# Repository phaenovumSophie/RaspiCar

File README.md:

# RaspiCar
A model car equipped with a Raspberry Pi, intended for experimenting with tools and algorithms for autonomous navigation

This is a simple platform for experimenting. At this stage clearly work in progress ...

The car is based on two stepper motors for the left and right driving wheel. In addition there is a free spinning wheel in the front. Driving direction is controlled by different speed settings for the motors. The car is capable of turning on the spot. Power is provided a by a LiPo battery of 3 cells.

Raspberry Pi:
=============
The Raspberry Pi provides navigation and overall management of the car. The navigations is based on the various sensors. The software is written primarily in Python. Prototype software is avaiable to support ultrasonic sensors, LiDAR, camera and a NRF24 module for remote control. There are also experiments with machine learning alogrithms (SciKit Learn). More to be developed and to follow.

Python files:
- io_ctrl.py - This module defines the I/Os for the Raspberry Pi and a tool to send commands to the motor driver via a serial interface
- much more to come ...

Motor Driver:
=============
In addition to the Raspberry Pi, there is a board comprising a 5V step down converter, a rp2040 microcontroller, a LCD and adapters for various devices such as LiDAR, distance sensors and more. The rp2040 generates the step and direction signals for the stepper motors, with this releasing the real time workload from the Raspberry Pi. The rp2040 interfaces with the Raspberry Pi via a serial interface running at115200 baud. The rp2040 also takes care of power management by raising a shutdown signal in case the battery voltage is running low. The software for the rp2040 is based on Arduino/C++

Arduino files for the motor driver:
- rp2040_motor_driver.ino: main program
- motors.cpp, motors.h: class to run the stepper motors
- display.cpp, display.h: class to run the display
- battery.cpp, battery.h: class to provide battery and power management

List of motor commands:
The Raspberry Pi sends commands via the serial interface and receives responses. This can easily by tested via a standard terminal tool (e.g. PUTTY).
- ME0,0 / ME1,1  - disables or enables motor A and B
- MP0,0 / MP1,1  - switches motor A and B on or off
- MD0,0 / MD1,1  - sets the direction of the motor (1 -> forward, 0 -> backward)
- MR<l>,<r> - sets the speed of the motors in rounds per minute. The range is 0 to 1500. Example: "MR200,500"
- DC - clears the display (title and message)
- DT - prints a title of up to 0 characters on line 1 of the display (maximum 20 characters)
- DM - prints a message of up to 40 character on line 2 and 3 of the display
- BV - returns the current battery voltage
- BS - returns the battery voltage and the system status, separated by comma 

List of system status:
  - 0 - STATUS_OK                   'OK' - all fine
  - 1 - STATUS_BAT_LOW              'BL' - Battery low, voltage below 10.5V
  - 2 - STATUS_BAT_SHUTDOWN         'BS' - Battery very low, shutdown requested due to low power, waiting for Raspi to respond
  - 3 - STATUS_BAT_EXTERNAL         'BE  - System running on 5V external power
  - 4 - STATUS_SHUTDOWN_REQUESTED   'SR' - Shutdwon requested by user, waiting for Raspi to respond
  - 5 - STATUS_SHUTDOWN_ACTIVE      'SX' - Shutdown in progress, power will be shut in less than 10 secs

SLW October 2022

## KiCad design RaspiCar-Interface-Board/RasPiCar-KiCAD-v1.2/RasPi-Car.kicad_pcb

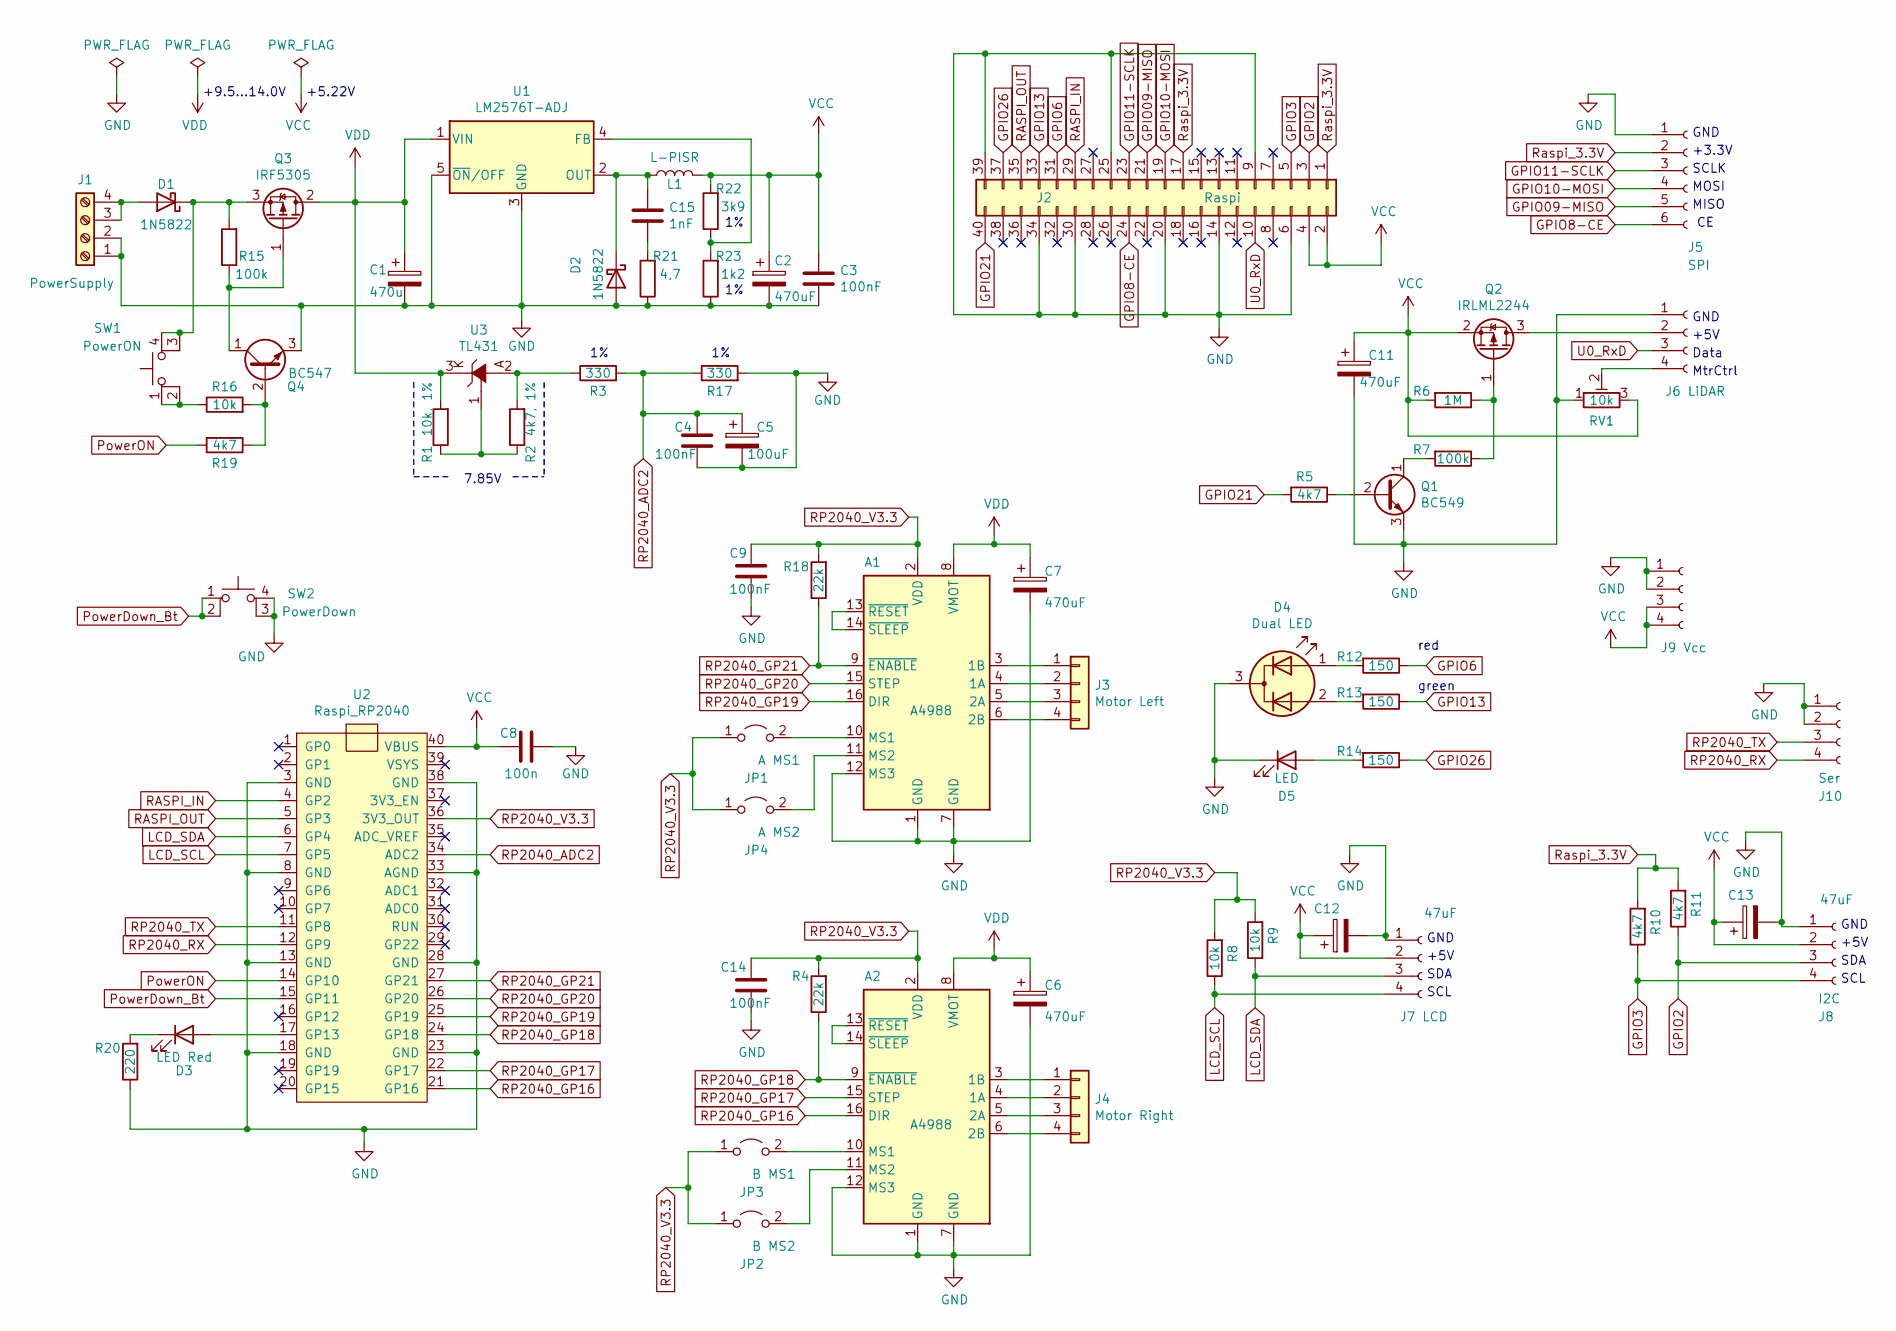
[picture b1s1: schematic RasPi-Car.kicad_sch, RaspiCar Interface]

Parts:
A1, A2: A4988; Pololu_Breakout-16_15.2x20.3mm
C1: 470u; CP_Radial_D8.0mm_P3.50mm
C2, C6, C7, C11: 470uF; CP_Radial_D8.0mm_P3.50mm
C3, C4, C9, C14: 100nF; C_Disc_D3.4mm_W2.1mm_P2.50mm
C5: 100uF; CP_Radial_D6.3mm_P2.50mm
C8: 100n; C_Disc_D3.4mm_W2.1mm_P2.50mm
C12, C13: 47uF; CP_Radial_D6.3mm_P2.50mm
C15: 1nF; C_Disc_D3.4mm_W2.1mm_P2.50mm
D1, D2: 1N5822; D_DO-201AE_P3.81mm_Vertical_KathodeUp
D3: LED Red; LED_D3.0mm
D4: Dual LED; LED_D3.0mm-3-center-kathode
D5: LED; LED_D3.0mm
J1: PowerSupply; ScrewTerminal_1x4
J2: Raspi; PinHeader_2x20_P2.54mm_Vertical
J3: Motor Left; PinHeader_1x04_P2.54mm_Vertical
J4: Motor Right; PinHeader_1x04_P2.54mm_Vertical
J5: SPI; PinHeader_1x06_P2.54mm_Vertical
J6: LiDAR; PinHeader_1x04_P2.54mm_Vertical
J7: LCD; PinHeader_1x04_P2.54mm_Vertical
J8: I2C; PinHeader_1x04_P2.54mm_Vertical
J9: Vcc; PinHeader_1x04_P2.54mm_Vertical
J10: Ser; PinHeader_1x04_P2.54mm_Vertical
JP1: A MS1; PinHeader_1x02_P2.54mm_Vertical
JP2: B MS2; PinHeader_1x02_P2.54mm_Vertical
JP3: B MS1; PinHeader_1x02_P2.54mm_Vertical
JP4: A MS2; PinHeader_1x02_P2.54mm_Vertical
L1: L-PISR; L-PISR-100
Q1: BC549; TO-92_HandSolder
Q2: IRLML2244; SOT-23
Q3: IRF5305; TO-220-3_Vertical
Q4: BC547; TO-92_HandSolder
R1: 10k, 1%; R_Axial_DIN0207_L6.3mm_D2.5mm_P7.62mm_Horizontal
R2: 4k7, 1%; R_Axial_DIN0207_L6.3mm_D2.5mm_P7.62mm_Horizontal
R3, R17: 330; R_Axial_DIN0207_L6.3mm_D2.5mm_P7.62mm_Horizontal
R4, R18: 22k; R_Axial_DIN0207_L6.3mm_D2.5mm_P7.62mm_Horizontal
R5, R10, R11, R19: 4k7; R_Axial_DIN0207_L6.3mm_D2.5mm_P7.62mm_Horizontal
R6: 1M; R_Axial_DIN0207_L6.3mm_D2.5mm_P7.62mm_Horizontal
R7, R15: 100k; R_Axial_DIN0207_L6.3mm_D2.5mm_P7.62mm_Horizontal
R8, R9, R16: 10k; R_Axial_DIN0207_L6.3mm_D2.5mm_P7.62mm_Horizontal
R12, R13: 150; R_Axial_DIN0207_L6.3mm_D2.5mm_P2.54mm_Vertical
R14: 150; R_Axial_DIN0207_L6.3mm_D2.5mm_P7.62mm_Horizontal
R20: 220; R_Axial_DIN0207_L6.3mm_D2.5mm_P7.62mm_Horizontal
R21: 4,7; R_Axial_DIN0207_L6.3mm_D2.5mm_P2.54mm_Vertical
R22: 3k9; R_Axial_DIN0207_L6.3mm_D2.5mm_P2.54mm_Vertical
R23: 1k2; R_Axial_DIN0207_L6.3mm_D2.5mm_P2.54mm_Vertical
RV1: 10k; R-Trim_horizontal
SW1: PowerON; SW_PUSH_6mm_H5mm
SW2: PowerDown; SW_PUSH_6mm_H5mm
U1: LM2576T-ADJ; TO-220-5_Vertical_tiny_heatsink
U2: Raspi_RP2040
U3: TL431; TO-92_HandSolder

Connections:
GND: A1.1 (GND), A1.7 (GND), A1.12 (MS3), A2.1 (GND), A2.7 (GND), A2.12 (MS3), C1.2, C2.2, C3.2, C4.1, C5.2, C6.2, C7.2, C8.1, C9.2, C11.2, C12.2, C13.2, C14.2, D2.2 (A), D4.3 (K), D5.1 (K), J1.1, J1.2, J2.6, J2.9, J2.14, J2.20, J2.25, J2.30, J2.34, J2.39, J5.1, J6.1, J7.1, J8.1, J9.1, J9.2, J10.1, J10.2, Q1.3 (E), Q4.3 (E), R17.2, R20.1, R21.1, R23.1, RV1.1, SW2.3 (K), SW2.4 (A), U1.3 (GND), U1.5 (~ON/OFF), U2.3 (GND), U2.8 (GND), U2.13 (GND), U2.18 (GND), U2.23 (GND), U2.28 (GND), U2.33 (AGND), U2.38 (GND)
GPIO2: J2.3, J8.3, R11.1
GPIO3: J2.5, J8.4, R10.1
GPIO6: J2.31, R12.1
GPIO8-CE: J2.24, J5.6
GPIO09-MISO: J2.21, J5.5
GPIO10-MOSI: J2.19, J5.4
GPIO11-SCLK: J2.23, J5.3
GPIO13: J2.33, R13.1
GPIO21: J2.40, R5.2
GPIO26: J2.37, R14.1
LCD_SCL: J7.4, R8.1, U2.7 (GP5)
LCD_SDA: J7.3, R9.1, U2.6 (GP4)
unnamed: A1.4 (1A), J3.2
unnamed: A1.3 (1B), J3.1
unnamed: A1.5 (2A), J3.3
unnamed: A1.6 (2B), J3.4
unnamed: A1.10 (MS1), JP1.2 (B)
unnamed: A1.11 (MS2), JP4.2 (B)
unnamed: A1.13 (~RESET), A1.14 (~SLEEP)
unnamed: A2.4 (1A), J4.2
unnamed: A2.3 (1B), J4.1
unnamed: A2.5 (2A), J4.3
unnamed: A2.6 (2B), J4.4
unnamed: A2.10 (MS1), JP3.2 (B)
unnamed: A2.11 (MS2), JP2.2 (B)
unnamed: A2.13 (~RESET), A2.14 (~SLEEP)
unnamed: C15.2, R21.2
unnamed: D1.2 (A), J1.3, J1.4
unnamed: D1.1 (K), Q3.3 (S), R15.2, SW1.3 (K), SW1.4 (A)
unnamed: C15.1, D2.1 (K), L1.1, U1.2 (OUT)
unnamed: D3.2 (A), U2.17 (GP13)
unnamed: D3.1 (K), R20.2
unnamed: D4.1 (A1), R12.2
unnamed: D4.2 (A2), R13.2
unnamed: D5.2 (A), R14.2
unnamed: J6.2, Q2.3 (D)
unnamed: J6.4, RV1.2
unnamed: Q1.2 (B), R5.1
unnamed: Q1.1 (C), R7.2
unnamed: Q2.1 (G), R6.1, R7.1
unnamed: Q3.1 (G), Q4.1 (C), R15.1
unnamed: Q4.2 (B), R16.2, R19.1
unnamed: R16.1, SW1.1, SW1.2
unnamed: R22.1, R23.2, U1.4 (FB)
unnamed: R2.2, R3.1, U3.2 (A)
unnamed: R1.1, R2.1, U3.1 (R)
PowerDown_Bt: SW2.1, SW2.2, U2.15 (GP11)
PowerON: R19.2, U2.14 (GP10)
RASPI_IN: J2.29, U2.4 (GP2)
RASPI_OUT: J2.35, U2.5 (GP3)
RP2040_ADC2: C4.2, C5.1, R3.2, R17.1, U2.34 (ADC2)
RP2040_GP16: A2.16 (DIR), U2.21 (GP16)
RP2040_GP17: A2.15 (STEP), U2.22 (GP17)
RP2040_GP18: A2.9 (~ENABLE), R4.1, U2.24 (GP18)
RP2040_GP19: A1.16 (DIR), U2.25 (GP19)
RP2040_GP20: A1.15 (STEP), U2.26 (GP20)
RP2040_GP21: A1.9 (~ENABLE), R18.1, U2.27 (GP21)
RP2040_RX: J10.4, U2.12 (GP9)
RP2040_TX: J10.3, U2.11 (GP8)
RP2040_V3.3: A1.2 (VDD), A2.2 (VDD), C9.1, C14.1, JP1.1 (A), JP2.1 (A), JP3.1 (A), JP4.1 (A), R4.2, R8.2, R9.2, R18.2, U2.36 (3V3_OUT)
Raspi_3.3V: J2.1, J2.17, J5.2, R10.2, R11.2
U0_RxD: J2.10, J6.3
VCC: C2.1, C3.1, C8.2, C11.1, C12.1, C13.1, J2.2, J2.4, J7.2, J8.2, J9.3, J9.4, L1.2, Q2.2 (S), R6.2, R22.2, RV1.3, U2.40 (VBUS)
VDD: A1.8 (VMOT), A2.8 (VMOT), C1.1, C6.1, C7.1, Q3.2 (D), R1.2, U1.1 (VIN), U3.3 (K)

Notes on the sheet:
SCL
+9.5...14.0V
+5V
7.85V
SDA
MtrCtrl
Data
SCLK
red
MISO
GND
+5.22V
+3.3V
MOSI
green

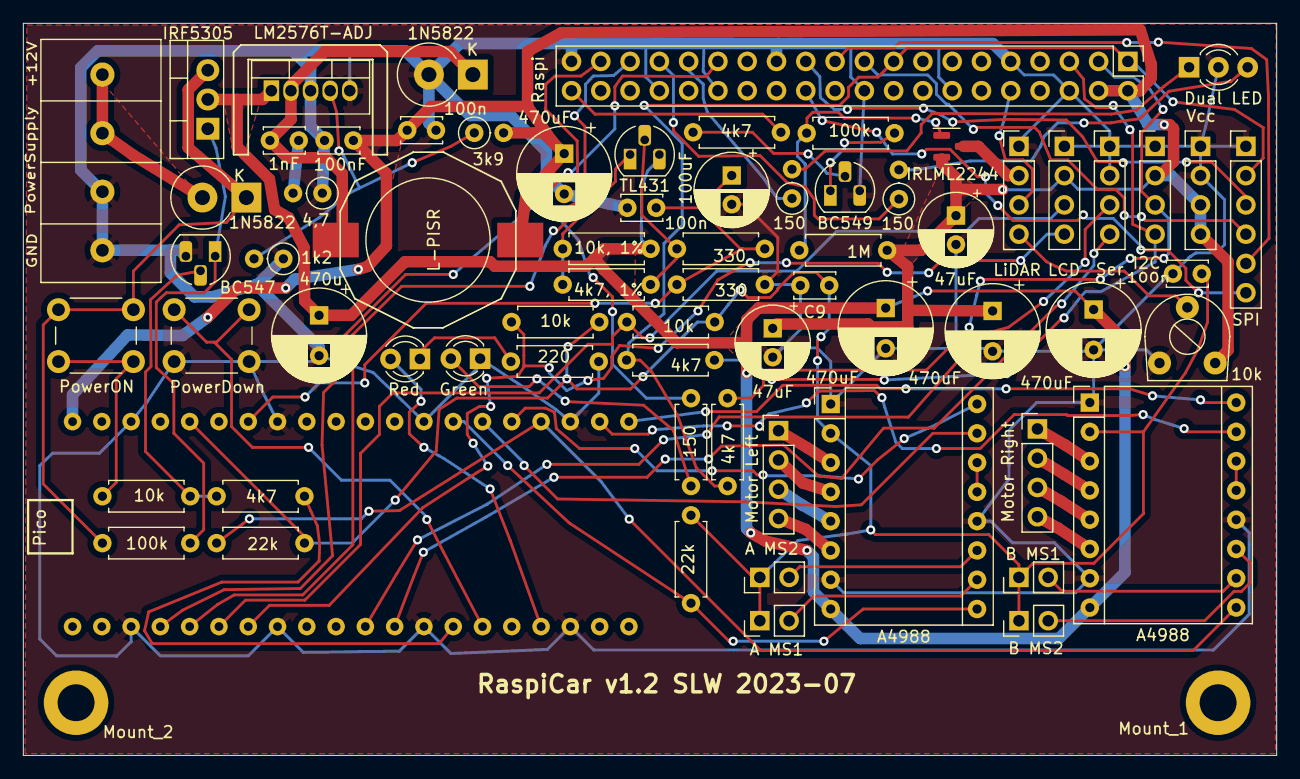
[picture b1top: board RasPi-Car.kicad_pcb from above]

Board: 2 copper layers, 108.7 x 63.5 mm, 71 parts (0 on the bottom side), 65 nets.

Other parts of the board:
Mount_1: Mount_1; MountingHole_3.2mm_M3_DIN965_Pad
Mount_2: Mount_2; MountingHole_3.2mm_M3_DIN965_Pad

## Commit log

2022-10-28 Version 0.1
2023-06-25 RaspiCar Controller added
2023-06-26 New version of Python scripts for the RaspiCar
    Python scripts for teh RaspiCar reworked
2023-06-27 Update raspicar_socket.py
    Bug fix at latency measurement
2023-06-28 Minor bug fixes
2023-07-15 Interface Board with KiCAD added
2023-07-15 Bug fix
2023-07-15 Bug fixes
2023-07-17 Pinout for the interface board added
2023-07-17 Interface board pinout added
2023-07-20 Foto added
2023-07-20 Fotos added
2023-12-01 raspicar_ioctrl2.py and raspicar_cameraadded
    The new version of IoCtrl does not need PIGPIO anymore.
